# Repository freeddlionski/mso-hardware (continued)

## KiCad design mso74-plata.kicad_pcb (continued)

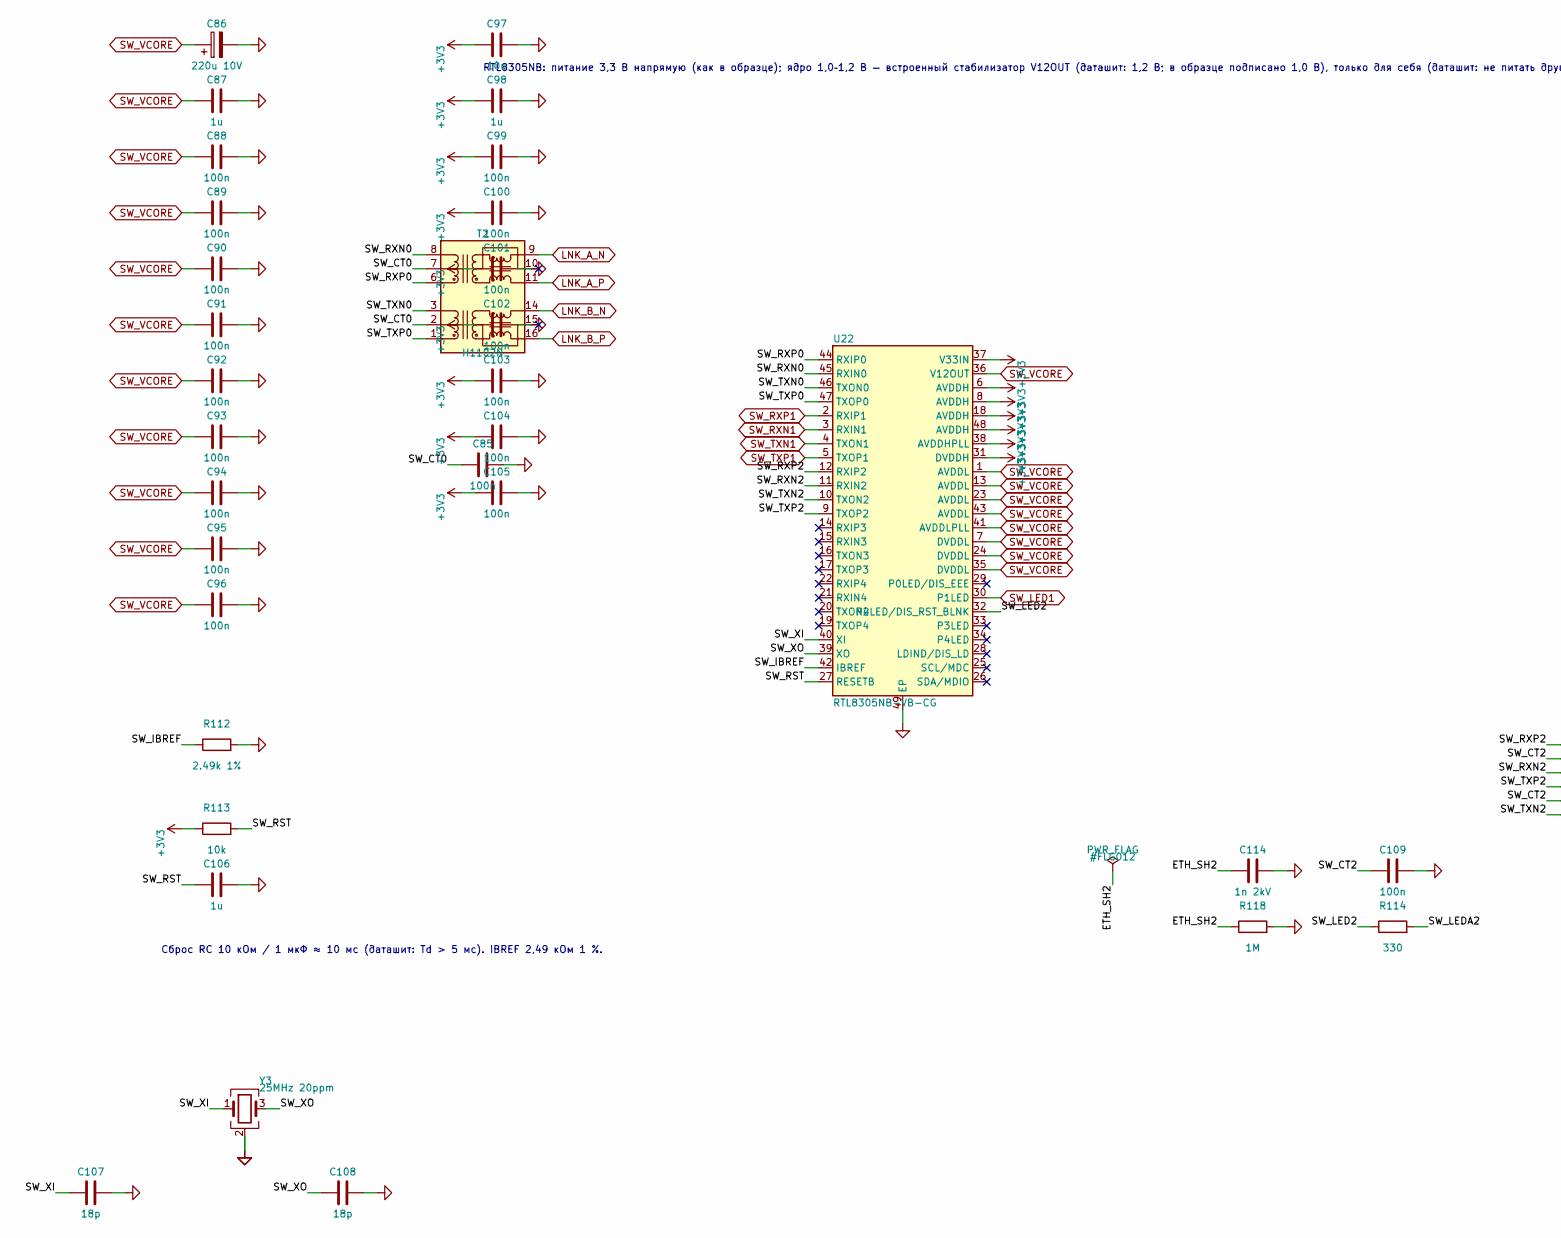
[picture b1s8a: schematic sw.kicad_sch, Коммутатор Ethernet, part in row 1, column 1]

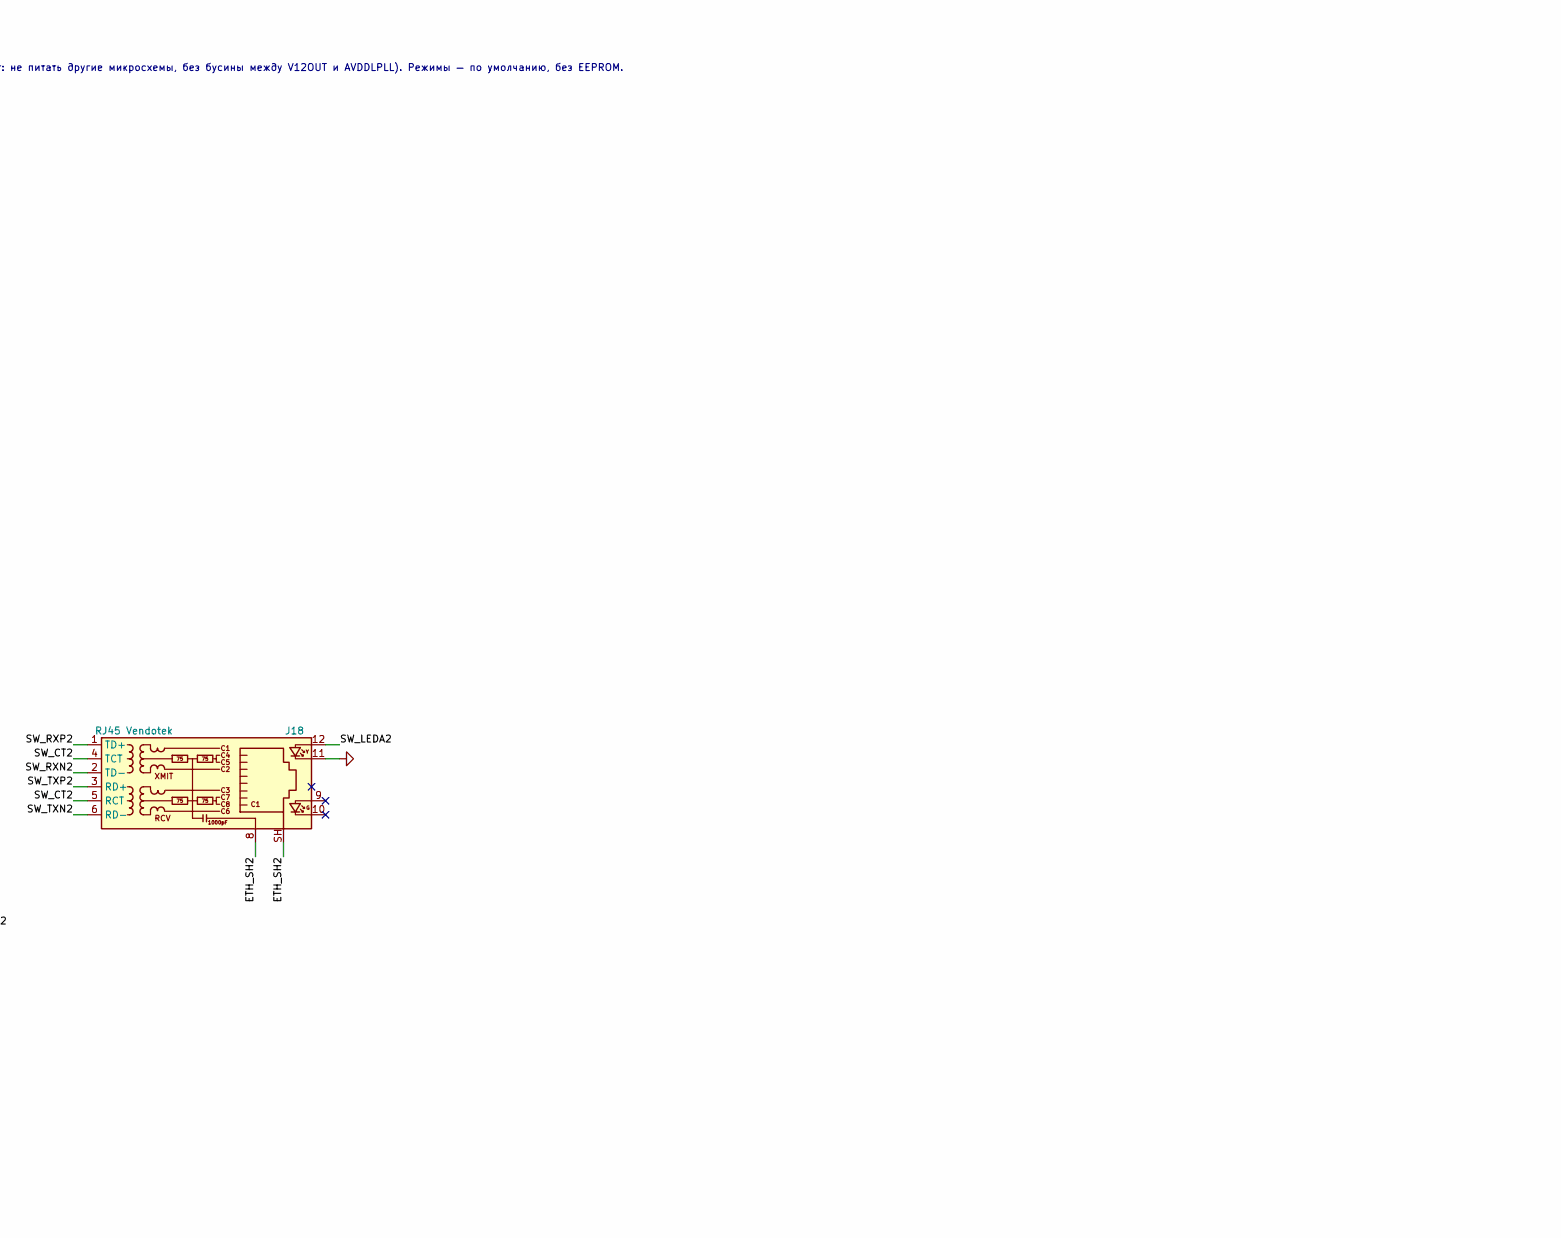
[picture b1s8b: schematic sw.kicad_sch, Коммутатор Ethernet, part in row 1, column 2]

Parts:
C85, C88, C89, C90, C91, C92, C93, C94, C95, C96, C99, C100, C101, C102, C103, C104, C105, C109: 100n; C_0603_1608Metric; MPN CC0603KRX7R9BB104; LCSC C14663
C86: 220u 10V; CP_Elec_6.3x5.4; MPN RVT220UF10V67RV0037; LCSC C2833309
C87, C98, C106: 1u; C_0603_1608Metric; MPN 0603X105K500NT; LCSC C157684
C97: 10u; C_0805_2012Metric; MPN CL21A106KOQNNNE; LCSC C1713
C107, C108: 18p; C_0603_1608Metric; MPN CL10C180JB8NNNC; LCSC C1647
C114: 1n 2kV; C_1206_3216Metric; MPN 1206B102K202NT; LCSC C9196
J18: RJ45 Vendotek; RJ45_Hanrun_HR911105A_Horizontal; MPN HR911105A; LCSC C12074
R112: 2.49k 1%; R_0603_1608Metric; MPN 0603WAD2491T5E; LCSC C407609
R113: 10k; R_0603_1608Metric; MPN 0603WAF1002T5E; LCSC C25804
R114: 330; R_0603_1608Metric; MPN 0603WAF3300T5E; LCSC C23138
R118: 1M; R_0603_1608Metric; MPN 0603WAF1004T5E; LCSC C22935
T2: H1102N; Transformer_Ethernet_CNDtek_H1102N; MPN CND-tek H1102N; LCSC C42418465
U22: RTL8305NB-VB-CG; QFN-48-1EP_6x6mm_P0.4mm_EP4.4x4.4mm; MPN RTL8305NB-VB-CG; LCSC C3010343
Y3: 25MHz 20ppm; Crystal_SMD_3225-4Pin_3.2x2.5mm; MPN X322525MOB4SI; LCSC C9006

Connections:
+3V3: C97.1, C98.1, C99.1, C100.1, C101.1, C102.1, C103.1, C104.1, C105.1, R113.1, U22.6 (AVDDH), U22.8 (AVDDH), U22.18 (AVDDH), U22.31 (DVDDH), U22.37 (V33IN), U22.38 (AVDDHPLL), U22.48 (AVDDH); also elsewhere on the board
/Коммутатор Ethernet/ETH_SH2: C114.1, J18.8, J18.SH, R118.1
/Коммутатор Ethernet/SW_CT0: C85.1, T2.2 (C_TD), T2.7 (C_RD)
/Коммутатор Ethernet/SW_CT2: C109.1, J18.4 (TCT), J18.5 (RCT)
/Коммутатор Ethernet/SW_IBREF: R112.1, U22.42 (IBREF)
/Коммутатор Ethernet/SW_LED2: R114.1, U22.32 (P2LED/DIS_RST_BLNK)
/Коммутатор Ethernet/SW_LEDA2: J18.12, R114.2
/Коммутатор Ethernet/SW_RST: C106.1, R113.2, U22.27 (RESETB)
/Коммутатор Ethernet/SW_RXN0: T2.8 (RD-), U22.45 (RXIN0)
/Коммутатор Ethernet/SW_RXN2: J18.2 (TD-), U22.11 (RXIN2)
/Коммутатор Ethernet/SW_RXP0: T2.6 (RD+), U22.44 (RXIP0)
/Коммутатор Ethernet/SW_RXP2: J18.1 (TD+), U22.12 (RXIP2)
/Коммутатор Ethernet/SW_TXN0: T2.3 (TD-), U22.46 (TXON0)
/Коммутатор Ethernet/SW_TXN2: J18.6 (RD-), U22.10 (TXON2)
/Коммутатор Ethernet/SW_TXP0: T2.1 (TD+), U22.47 (TXOP0)
/Коммутатор Ethernet/SW_TXP2: J18.3 (RD+), U22.9 (TXOP2)
/Коммутатор Ethernet/SW_XI: C107.1, U22.40 (XI), Y3.1
/Коммутатор Ethernet/SW_XO: C108.1, U22.39 (XO), Y3.3
GND: C85.2, C86.2, C87.2, C88.2, C89.2, C90.2, C91.2, C92.2, C93.2, C94.2, C95.2, C96.2, C97.2, C98.2, C99.2, C100.2, C101.2, C102.2, C103.2, C104.2, C105.2, C106.2, C107.2, C108.2, C109.2, C114.2, J18.11, R112.2, R118.2, U22.49 (EP), Y3.2 (G), Y3.4 (G); also elsewhere on the board
LNK_A_N: T2.9 (RX-); also elsewhere on the board
LNK_A_P: T2.11 (RX+); also elsewhere on the board
LNK_B_N: T2.14 (TX-); also elsewhere on the board
LNK_B_P: T2.16 (TX+); also elsewhere on the board
SW_LED1: U22.30 (P1LED); also elsewhere on the board
SW_RXN1: U22.3 (RXIN1); also elsewhere on the board
SW_RXP1: U22.2 (RXIP1); also elsewhere on the board
SW_TXN1: U22.4 (TXON1); also elsewhere on the board
SW_TXP1: U22.5 (TXOP1); also elsewhere on the board
SW_VCORE: C86.1, C87.1, C88.1, C89.1, C90.1, C91.1, C92.1, C93.1, C94.1, C95.1, C96.1, U22.1 (AVDDL), U22.7 (DVDDL), U22.13 (AVDDL), U22.23 (AVDDL), U22.24 (DVDDL), U22.35 (DVDDL), U22.36 (V12OUT), U22.41 (AVDDLPLL), U22.43 (AVDDL); also elsewhere on the board

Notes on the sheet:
RTL8305NB: питание 3,3 В напрямую (как в образце); ядро 1,0–1,2 В — встроенный стабилизатор V12OUT (даташит: 1,2 В; в образце подписано 1,0 В), только для себя (даташит: не питать другие микросхемы, без бусины между V12OUT и AVDDLPLL). Режимы — по умолчанию, без EEPROM.
Сброс RC 10 кОм / 1 мкФ ≈ 10 мс (даташит: Td > 5 мс). IBREF 2,49 кОм 1 %.

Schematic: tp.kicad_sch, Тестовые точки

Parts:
TP1: VIN_F вход после предохранителя; TestPoint_Pad_D1.5mm
TP2: +24V_P после eFuse; TestPoint_Pad_D1.5mm
TP3: +12V; TestPoint_Pad_D1.5mm
TP4: +5V; TestPoint_Pad_D1.5mm
TP5: +3V3; TestPoint_Pad_D1.5mm
TP6: +5V_LCD1 табло 1; TestPoint_Pad_D1.5mm
TP7: +5V_LCD2 табло 2; TestPoint_Pad_D1.5mm
TP8: SW_VCORE ядро коммутатора; TestPoint_Pad_D1.5mm
TP9, TP10, TP11: GND; TestPoint_Pad_D1.5mm
TP12: ESP_EN сброс ESP32; TestPoint_Pad_D1.5mm
TP13: ESP_IO0 BOOT; TestPoint_Pad_D1.5mm
TP14: U0_TX UART0; TestPoint_Pad_D1.5mm
TP15: U0_RX UART0; TestPoint_Pad_D1.5mm
TP16: MDB_TX; TestPoint_Pad_D1.5mm
TP17: MDB_RX; TestPoint_Pad_D1.5mm
TP18: RS485_A; TestPoint_Pad_D1.5mm
TP19: RS485_B; TestPoint_Pad_D1.5mm
TP20: RTC_SCL I2C; TestPoint_Pad_D1.5mm
TP21: RTC_SDA I2C; TestPoint_Pad_D1.5mm

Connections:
+3V3: TP5.1; also elsewhere on the board
+5V: TP4.1; also elsewhere on the board
+5V_LCD1: TP6.1; also elsewhere on the board
+5V_LCD2: TP7.1; also elsewhere on the board
+12V: TP3.1; also elsewhere on the board
+24V_P: TP2.1; also elsewhere on the board
ESP_EN: TP12.1; also elsewhere on the board
ESP_IO0: TP13.1; also elsewhere on the board
GND: TP9.1, TP10.1, TP11.1; also elsewhere on the board
MDB_RX: TP17.1; also elsewhere on the board
MDB_TX: TP16.1; also elsewhere on the board
RS485_A: TP18.1; also elsewhere on the board
RS485_B: TP19.1; also elsewhere on the board
RTC_SCL: TP20.1; also elsewhere on the board
RTC_SDA: TP21.1; also elsewhere on the board
SW_VCORE: TP8.1; also elsewhere on the board
U0_RX: TP15.1; also elsewhere on the board
U0_TX: TP14.1; also elsewhere on the board
VIN_F: TP1.1; also elsewhere on the board

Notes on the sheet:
Тестовые точки: площадки под щуп, не паяются (в BOM нет).

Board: 4 copper layers, 396 parts (0 on the bottom side), 264 nets, no tracks yet.

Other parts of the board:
H1, H2, H3, H4: MountingHole_3.2mm_M3

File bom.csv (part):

"Reference","Value","Footprint","LCSC","QUANTITY"
"BT1","CR2032","Battery:BatteryHolder_MYOUNG_BS-07-A1BJ001_CR2032","C2979167","1"
"C1,C3","100n 100V","Capacitor_SMD:C_0603_1608Metric","C15725","2"
"C2,C63","22n","Capacitor_SMD:C_0603_1608Metric","C277528","2"
"C4","1u 50V","Capacitor_SMD:C_1206_3216Metric","C1848","1"
"C5","100u 50V","Capacitor_SMD:CP_Elec_10x10.5","C5158069","1"
"C6,C12,C18,C24,C25,C35,C36,C110,C111","10u 50V","Capacitor_SMD:C_1210_3225Metric","C77102","9"
"C7,C13,C19,C26,C27,C37,C38","100n 50V","Capacitor_SMD:C_0603_1608Metric","C14663","7"
"C8,C11,C14,C17,C20,C23,C29,C40,C48,C49,C51,C54-C57,C67,C68,C70-C76,C79,C80,C82-C85,C88-C96,C99-C105,C109,C113","100n","Capacitor_SMD:C_0603_1608Metric","C14663","48"
"C9,C10,C115","22u","Capacitor_SMD:C_1210_3225Metric","C52306","3"
"C15,C16,C21,C22,C46","22u","Capacitor_SMD:C_1206_3216Metric","C90146","5"
"C28,C39,C50,C87,C98,C106","1u","Capacitor_SMD:C_0603_1608Metric","C157684","6"
"C30-C33,C41-C44","47u 10V","Capacitor_SMD:C_1210_3225Metric","C76680","8"
"C34,C45","470u 16V","Capacitor_SMD:CP_Elec_10x10.5","C2905295","2"
"C47,C52,C53,C58,C97","10u","Capacitor_SMD:C_0805_2012Metric","C1713","5"
"C59","4.7u","Capacitor_SMD:C_0805_2012Metric","C1779","1"
"C60,C66,C77,C78","10n","Capacitor_SMD:C_0603_1608Metric","C57112","4"
"C61,C62,C107,C108","18p","Capacitor_SMD:C_0603_1608Metric","C1647","4"
"C64,C65","6.8n","Capacitor_SMD:C_0603_1608Metric","C107097","2"
"C69","100n 100V","Capacitor_SMD:C_0805_2012Metric","C344180","1"
"C86","220u 10V","Capacitor_SMD:CP_Elec_6.3x5.4","C2833309","1"
"C112,C114","1n 2kV","Capacitor_SMD:C_1206_3216Metric","C9196","2"
"D1","SMCJ33CA","Diode_SMD:D_SMC","C224050","1"
"D2","4.7V","Diode_SMD:D_SOD-123","C22395547","1"
"D3-D10","зелёный","LED_SMD:LED_0603_1608Metric","C2289","8"
"D11","красный TX","LED_SMD:LED_0603_1608Metric","C2286","1"
"D12","зелёный RX","LED_SMD:LED_0603_1608Metric","C2289","1"
"D13,D14","SMAJ36CA","Diode_SMD:D_SMA","C5249597","2"
"D15,D16","SMAJ8.0CA","Diode_SMD:D_SMA","C148237","2"
"D17,D21","BAT46WJ","Diode_SMD:D_SOD-323F","C114696","2"
"D19,D20,D24,D26,D28,D32,D35,D38,D41,D44-D47","SMAJ33A","Diode_SMD:D_SMA","C223988","13"
"D22,D30,D34,D37,D40,D43","BAT54S","Package_TO_SOT_SMD:SOT-23","C47546","6"
"D23,D25,D48,D49","1N4148W","Diode_SMD:D_SOD-123","C81598","4"
"D27","SS34","Diode_SMD:D_SMA","C8678","1"
"D29,D33,D36,D39,D42","BAT46W","Diode_SMD:D_SOD-123","C7420332","5"
"D31","BAT54C","Package_TO_SOT_SMD:SOT-23","C2135","1"
"D50","1N4148WS","Diode_SMD:D_SOD-323","C2128","1"
"F1","7.5A","Fuse:Fuseholder_Blade_Mini_Keystone_3568","C3205378","1"
"F2,F15-F18","1.1A удерж.","Fuse:Fuse_2920_7451Metric","C315903","5"
"F3,F8,F19","1.5A удерж.","Fuse:Fuse_2920_7451Metric","C6165178","3"
"F6","200mA удерж.","Fuse:Fuse_1812_4532Metric","C315900","1"
"F7,F9","100mA удерж.","Fuse:Fuse_1206_3216Metric","C70065","2"
"F10-F14","50mA удерж.","Fuse:Fuse_1206_3216Metric","C315892","5"
"FB1","600R@100MHz","Inductor_SMD:L_0805_2012Metric","C1017","1"
"J1","Питание +24V / GND","mso74:KANGNEX_WJ2EDGRC_1x02_P5.08mm_Drill1.7","C3697","1"
"J2","Vendotek: +24V / GND","mso74:KANGNEX_WJ2EDGRC_1x02_P5.08mm_Drill1.7","C3697","1"
"J3","Табло 1: +5V / GND","TerminalBlock_Phoenix:TerminalBlock_Phoenix_MKDS-1,5-2-5.08_1x02_P5.08mm_Horizontal","C8465","1"
"J4","Табло 2: +5V / GND","TerminalBlock_Phoenix:TerminalBlock_Phoenix_MKDS-1,5-2-5.08_1x02_P5.08mm_Horizontal","C8465","1"
"J5","USB-C","Connector_USB:USB_C_Receptacle_HCTL_HC-TYPE-C-16P-01A","C2894897","1"
"J7","RJ45 Сеть","Connector_RJ:RJ45_Hanrun_HR911105A_Horizontal","C12074","1"
"J8","RS-485: A / B / GND","mso74:KANGNEX_WJ15EDGRC_1x03_P3.81mm_Drill1.4","C8406","1"
"J9","Vendotek RS-232: TXD / RXD / GND","mso74:KANGNEX_WJ15EDGRC_1x03_P3.81mm_Drill1.4","C8406","1"
"J10","MDB Mini-Fit Jr 2×3","Connector_Molex:Molex_Mini-Fit_Jr_5566-06A_2x03_P4.20mm_Vertical","C20539148","1"
"J11","Монетник: +12V / GND / ИМП / БЛОК","mso74:KANGNEX_WJ15EDGRC_1x04_P3.81mm_Drill1.4","C7245","1"
"J12","Купюрник имп.: +24V / +12V / GND / ИМП","mso74:KANGNEX_WJ15EDGRC_1x04_P3.81mm_Drill1.4","C7245","1"
"J13","Сервис: КН / GND","mso74:KANGNEX_WJ15EDGRC_1x02_P3.81mm_Drill1.4","C8387","1"
"J14","HUB75 IDC-16","Connector_IDC:IDC-Header_2x08_P2.54mm_Vertical","C3406","1"
"J15","Входы: ВХ1–ВХ4 / GND / GND","mso74:KANGNEX_WJ15EDGRC_1x06_P3.81mm_Drill1.4","C7246","1"
"J16","Выходы: +24V / ВЫХ1–ВЫХ4 / GND","mso74:KANGNEX_WJ15EDGRC_1x06_P3.81mm_Drill1.4","C7246","1"
"J18","RJ45 Vendotek","Connector_RJ:RJ45_Hanrun_HR911105A_Horizontal","C12074","1"
"JP1","Терминатор 120 Ом","Connector_PinHeader_2.54mm:PinHeader_1x02_P2.54mm_Vertical","C492401","1"
"L1","10u 15A","Inductor_SMD:L_Bourns_SRP1245A","C840531","1"
"L2,L4,L5","6.8u 18A","Inductor_SMD:L_Bourns_SRP1245A","C2041326","3"
"L3","4.7u 10A","Inductor_SMD:L_Bourns_SRP7028A_7.3x6.6mm","C840529","1"
"Q1","CSD19534Q5A","mso74:Texas_DQJ_VSONP-8_5x6mm_CSD19534Q5A","C114200","1"
"Q2","2N7002","Package_TO_SOT_SMD:SOT-23","C85049","1"
"Q3,Q4,Q10","MMBT3904","Package_TO_SOT_SMD:SOT-23","C20526","3"
"Q5-Q9","BSP75N","mso74:SOT-223-3_TabPin3_BSP75N","C114056","5"
"Q11","PBSS5540X","Package_TO_SOT_SMD:SOT-89-3","C455078","1"
"Q12","MMBT3906","Package_TO_SOT_SMD:SOT-23","C916375","1"
"R1","390k 1%","Resistor_SMD:R_0603_1608Metric","C23150","1"
"R2","19.1k 1%","Resistor_SMD:R_0603_1608Metric","C22897","1"
"R3","15k 1%","Resistor_SMD:R_0603_1608Metric","C22809","1"
"R4","3k 1%","Resistor_SMD:R_0603_1608Metric","C4211","1"
"R5,R11,R13,R16,R18,R21,R23,R26,R33,R105,R107,R109,R111,R116","100k","Resistor_SMD:R_0603_1608Metric","C25803","14"
"R6","150k","Resistor_SMD:R_0603_1608Metric","C22807","1"
"R7,R27,R34,R40-R43,R55,R67,R70,R72,R75,R84,R93,R95,R97,R99-R103,R113,R117,R121","10k","Resistor_SMD:R_0603_1608Metric","C25804","24"
"R8-R10","22k","Resistor_SMD:R_0603_1608Metric","C31850","3"
"R12,R17,R22","8.66k","Resistor_SMD:R_0603_1608Metric","C23114","3"
"R14","5.23k 1%","Resistor_SMD:R_0603_1608Metric","C23068","1"
"R15,R20,R25","2.2k","Resistor_SMD:R_0603_1608Metric","C4190","3"
"R19","13.7k 1%","Resistor_SMD:R_0603_1608Metric","C22793","1"
"R24","22.1k 1%","Resistor_SMD:R_0603_1608Metric","C2960862","1"
"R28,R35","33.2k 1%","Resistor_SMD:R_0603_1608Metric","C185338","2"
"R29,R36","0","Resistor_SMD:R_0603_1608Metric","C21189","2"
"R30,R37","100k 1%","Resistor_SMD:R_0603_1608Metric","C25803","2"
"R31,R38","24.9k 1%","Resistor_SMD:R_0603_1608Metric","C137761","2"
"R32,R39,R56,R57,R65,R68,R71,R120","1k","Resistor_SMD:R_0603_1608Metric","C21190","8"
"R44,R45","5.1k","Resistor_SMD:R_0603_1608Metric","C23186","2"
"R46","12.4k 1%","Resistor_SMD:R_0603_1608Metric","C22865","1"
"R47,R115,R118","1M","Resistor_SMD:R_0603_1608Metric","C22935","3"
"R48,R49","49.9 1%","Resistor_SMD:R_0603_1608Metric","C23185","2"
"R50","10","Resistor_SMD:R_0603_1608Metric","C22859","1"
"R51-R53","82","Resistor_SMD:R_0603_1608Metric","C23255","3"
"R54,R74,R92,R94,R96,R98,R114","330","Resistor_SMD:R_0603_1608Metric","C23138","7"
"R58","120","Resistor_SMD:R_0805_2012Metric","C17437","1"
"R61","2.2k 1W","Resistor_SMD:R_2512_6332Metric","C453411","1"
"R62","1k 1W","Resistor_SMD:R_2512_6332Metric","C453362","1"
"R63","0","Resistor_SMD:R_0805_2012Metric","C17477","1"
"R64","91 1%","Resistor_SMD:R_1206_3216Metric","C137223","1"
"R66,R69","1.5k","Resistor_SMD:R_0603_1608Metric","C22843","2"
"R73,R104,R106,R108,R110","100","Resistor_SMD:R_0603_1608Metric","C22775","5"
"R76-R83,R85-R89","33","Resistor_SMD:R_0603_1608Metric","C23140","13"
"R90,R91,R119","4.7k","Resistor_SMD:R_0603_1608Metric","C23162","3"
"R112","2.49k 1%","Resistor_SMD:R_0603_1608Metric","C407609","1"
"R122","10","Resistor_SMD:R_0805_2012Metric","C17415","1"
"SW1","RESET","Button_Switch_SMD:SW_SPST_TL3342","C2886897","1"
"SW2","BOOT","Button_Switch_SMD:SW_SPST_TL3342","C2886897","1"
"SW3","СЕРВИС","Button_Switch_SMD:SW_SPST_TL3342","C2886897","1"
"T1,T2","H1102N","Transformer_SMD:Transformer_Ethernet_CNDtek_H1102N","C42418465","2"
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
